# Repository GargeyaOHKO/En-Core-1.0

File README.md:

---

# **Buck Converter Design: En-Core 1.0**

## **Introduction**
This project involves designing a non-isolated buck converter that steps down a 24V input to a 5V output with an efficiency of at least 90%. The buck converter is essential in many power conversion applications, such as power supplies and electric vehicles. 

### **Key Specifications:**
- **Input Voltage (Vin):** 24V (±2% tolerance)
- **Output Voltage (Vout):** 5V (±0.01V)
- **Input Current:** 1A max
- **Maximum Output Current:** 4.32A
- **Efficiency:** ≥ 90%
- **Form Factor:** Max PCB size of 10 cm x 5 cm

---

## **Theoretical Background**
A buck converter reduces the input voltage to a lower output voltage by switching a MOSFET on and off. The energy is stored in an inductor and smoothed out by a capacitor. The main components are:
- **Schottky Diode (1N5817):** The diode is forward biased when the NMOS is open switch, hence it allows the flow of current through it. When NMOS is closed, it is reverse biased, hence inductor starts storing energy. It also minimizes energy losses as compared to conventional diodes.
- **PWM Source (NE555 Timer):** Generates the switching signal of frequency 500kHz and Duty cycle(20.8%) to switch the circuit between input voltage and Schottky Diode.
- **Inductor and Capacitor:** For storing energy in the form of magnetic field and powering the circuit when NMOS is open switch, an inductor is used with ripple current = 0.2 * I_maxout. The capacitor is used for output voltage smoothing.

### **Efficiency Calculation:**
Efficiency depends on losses in the MOSFET (switching and conduction losses), inductor, and other components.

---

## **Simulation and Testing**

The circuit was simulated to verify the design, focusing on:
- Input voltage (24V DC)
- PWM signal generated by the NE555 (duty cycle 20.8%)
- Output voltage (5V with 0.02V ripple)

**Simulation Graphs:**
- **Green:** 24V input voltage
- **Blue:** PWM signal from the NE555 timer
- **Red:** 5V output DC voltage

---

## **Schematic and PCB Design**
- **Schematic:** Designed using KiCad, featuring a PWM generator (NE555), MOSFET, Schottky diode, inductor, and output capacitor.
- **PCB Design:** A dual-layer design to ensure proper thermal management, minimized noise, and correct trace width for current handling.

---

## **Conclusion**
The buck converter successfully steps down 24V to 5V with over 90% efficiency, meeting all design and dimensional constraints.

---

## **Project Links**
- [GitHub Repository](https://github.com/GargeyaOHKO/En-Core-1.0)
- [YouTube Simulation Video](https://youtu.be/STvGI6kvZm8)

---

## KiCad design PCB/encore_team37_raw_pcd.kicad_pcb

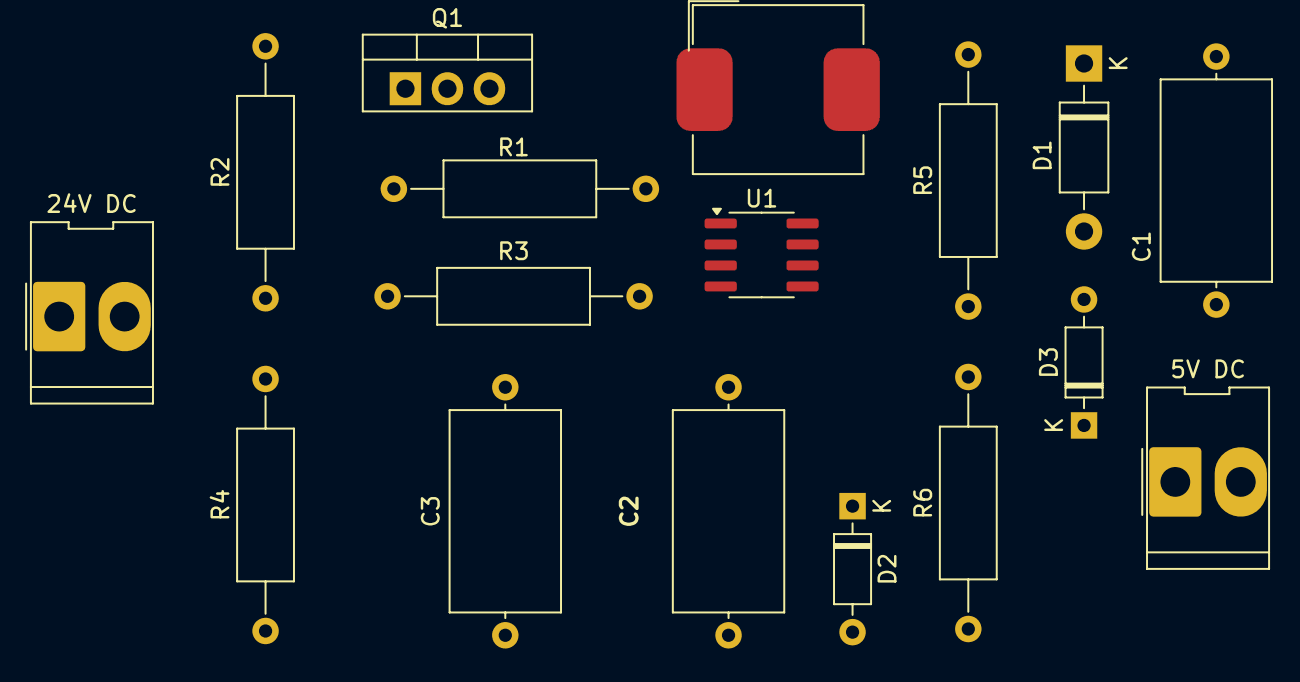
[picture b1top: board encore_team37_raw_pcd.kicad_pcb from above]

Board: 2 copper layers, 17 parts (0 on the bottom side), 11 nets, no tracks yet.

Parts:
5V DC: 5V DC; Molex_KK-396_5273-02A_1x02_P3.96mm_Vertical
24V DC: 24V DC; Molex_KK-396_5273-02A_1x02_P3.96mm_Vertical
C1: 10.8uF; C_Axial_L12.0mm_D6.5mm_P15.00mm_Horizontal
C2: 0.05uF; C_Axial_L12.0mm_D6.5mm_P15.00mm_Horizontal
C3: 0.01uF; C_Axial_L12.0mm_D6.5mm_P15.00mm_Horizontal
D1: 1N5817; D_DO-41_SOD81_P10.16mm_Horizontal
D2, D3: 1N914; D_DO-35_SOD27_P7.62mm_Horizontal
L1: 9.15uH; L_Bourns_SRP1050WA
Q1: IRF540N; TO-220-3_Vertical
R1: 3.6k; R_Axial_DIN0309_L9.0mm_D3.2mm_P15.24mm_Horizontal
R2, R3, R4, R6: 10k; R_Axial_DIN0309_L9.0mm_D3.2mm_P15.24mm_Horizontal
R5: 2.7k; R_Axial_DIN0309_L9.0mm_D3.2mm_P15.24mm_Horizontal
U1: NE555D; SOIC-8_3.9x4.9mm_P1.27mm

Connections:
GND: 5V DC.2, 24V DC.1, C1.2, C2.2, C3.2, D1.2 (A), R3.2, R4.1, U1.1 (GND)
unnamed: 24V DC.2, Q1.2 (D), R2.2
unnamed: 5V DC.1, C1.1, L1.2
unnamed: D1.1 (K), L1.1, Q1.3 (S)
unnamed: C2.1, D2.2 (A), D3.1 (K), U1.2 (TR), U1.6 (THR)
unnamed: D2.1 (K), R6.1
unnamed: D3.2 (A), R5.2, R6.2, U1.7 (DIS)
unnamed: Q1.1 (G), R1.2, R3.1
unnamed: C3.1, U1.5 (CV)
unnamed: R1.1, U1.3 (Q)
unnamed: R2.1, R4.2, R5.1, U1.4 (R), U1.8 (VCC)

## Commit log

2024-09-26 Rename encore_new_!.asc to encore_new_.asc
2024-09-26 Rename encore_new_!.raw to encore_new_.raw
2024-09-26 Rename encore_new_!.op.raw to encore_new_.op.raw
2024-09-26 Rename encore_new_!.net to encore_new_.net
2024-09-26 Rename encore_new_!.log to encore_new_.log
